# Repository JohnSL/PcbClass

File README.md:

# PcbClass
Material for an intro to PCB class

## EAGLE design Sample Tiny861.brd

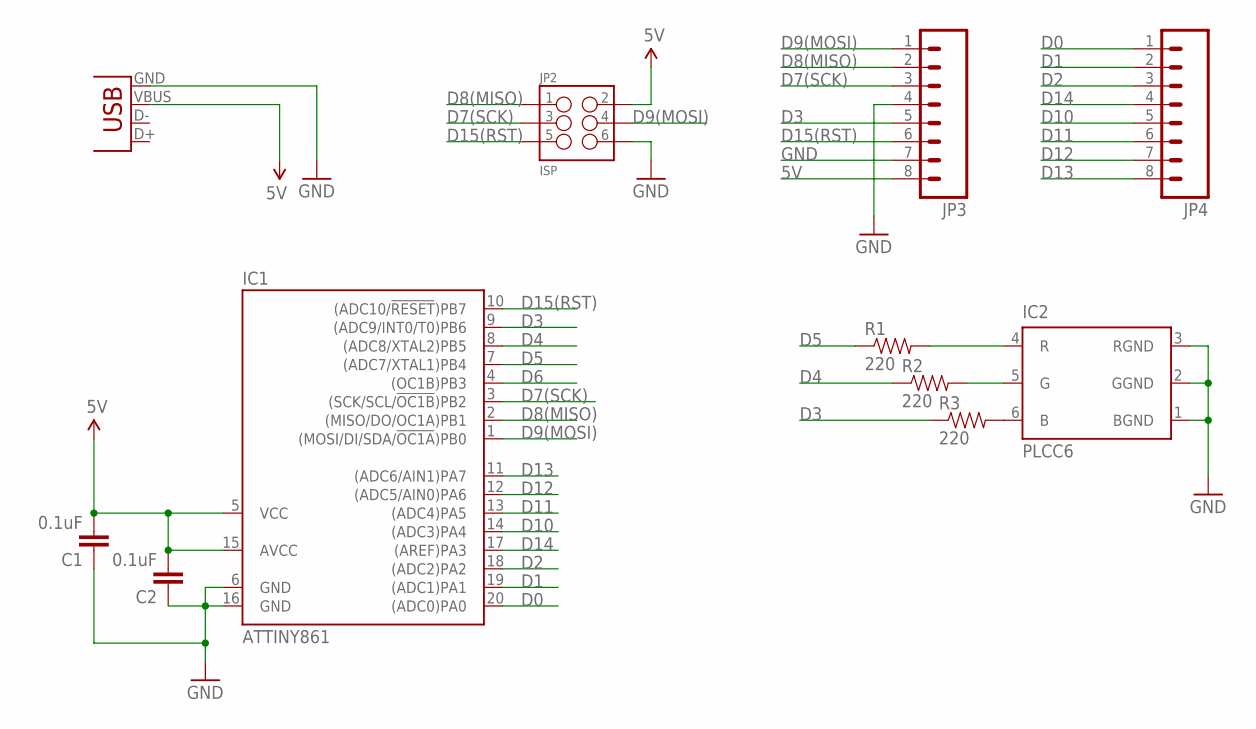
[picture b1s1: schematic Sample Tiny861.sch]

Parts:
C1, C2: 0.1uF; 0603-CAP
IC1: ATTINY861; SO20L
IC2: PLCC6
JP1: USBSMD; USB-MINIB
JP2: ISP; 2X3
JP3, JP4: M08; 1X08_PIN1_NO_SILK
R1, R2, R3: 220; 0603-RES

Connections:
5V: C1.2, C2.2, IC1.5 (VCC), IC1.15 (AVCC), JP1.VBUS, JP2.2, JP3.8
D0: IC1.20 ((ADC0)PA0), JP4.1
D1: IC1.19 ((ADC1)PA1), JP4.2
D2: IC1.18 ((ADC2)PA2), JP4.3
D3: IC1.9 ((ADC9/INT0/T0)PB6), JP3.5, R3.1
D4: IC1.8 ((ADC8/XTAL2)PB5), R2.1
D5: IC1.7 ((ADC7/XTAL1)PB4), R1.1
D6: IC1.4 ((OC1B)PB3)
D7(SCK): IC1.3 ((SCK/SCL/!OC1B!)PB2), JP2.3, JP3.3
D8(MISO): IC1.2 ((MISO/DO/OC1A)PB1), JP2.1, JP3.2
D9(MOSI): IC1.1 ((MOSI/DI/SDA/!OC1A!)PB0), JP2.4, JP3.1
D10: IC1.14 ((ADC3)PA4), JP4.5
D11: IC1.13 ((ADC4)PA5), JP4.6
D12: IC1.12 ((ADC5/AIN0)PA6), JP4.7
D13: IC1.11 ((ADC6/AIN1)PA7), JP4.8
D14: IC1.17 ((AREF)PA3), JP4.4
D15(RST): IC1.10 ((ADC10/!RESET!)PB7), JP2.5, JP3.6
GND: C1.1, C2.1, IC1.6 (GND), IC1.16 (GND), IC2.1 (BGND), IC2.2 (GGND), IC2.3 (RGND), JP1.GND, JP2.6, JP3.4, JP3.7
unnamed: IC2.4 (R), R1.2
unnamed: IC2.5 (G), R2.2
unnamed: IC2.6 (B), R3.2

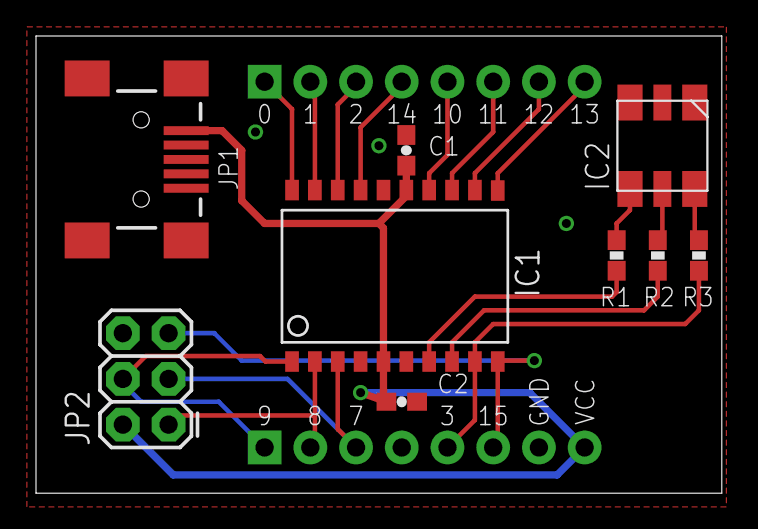
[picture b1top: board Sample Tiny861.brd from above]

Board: 2 copper layers, 38.1 x 25.4 mm, 11 parts (0 on the bottom side), 20 nets.

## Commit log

2015-04-25 Simple ATTiny861 board
    This is a very simple board designed for teaching a class on PCB design

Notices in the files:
parts and their libraries:
SparkFun-Capacitors: Licensing: Creative Commons ShareAlike 4.0 International - https://creativecommons.org/licenses/by-sa/4.0
